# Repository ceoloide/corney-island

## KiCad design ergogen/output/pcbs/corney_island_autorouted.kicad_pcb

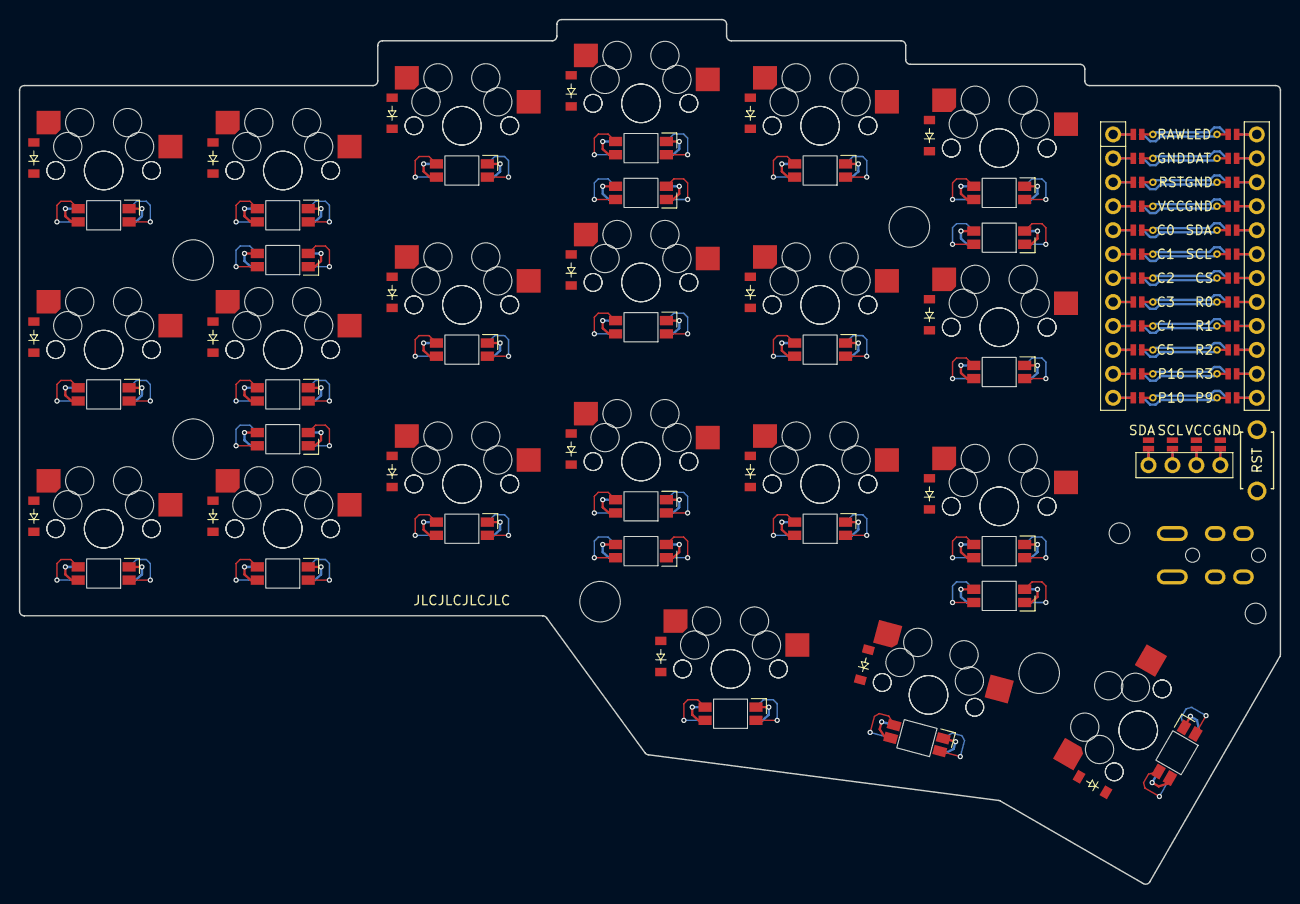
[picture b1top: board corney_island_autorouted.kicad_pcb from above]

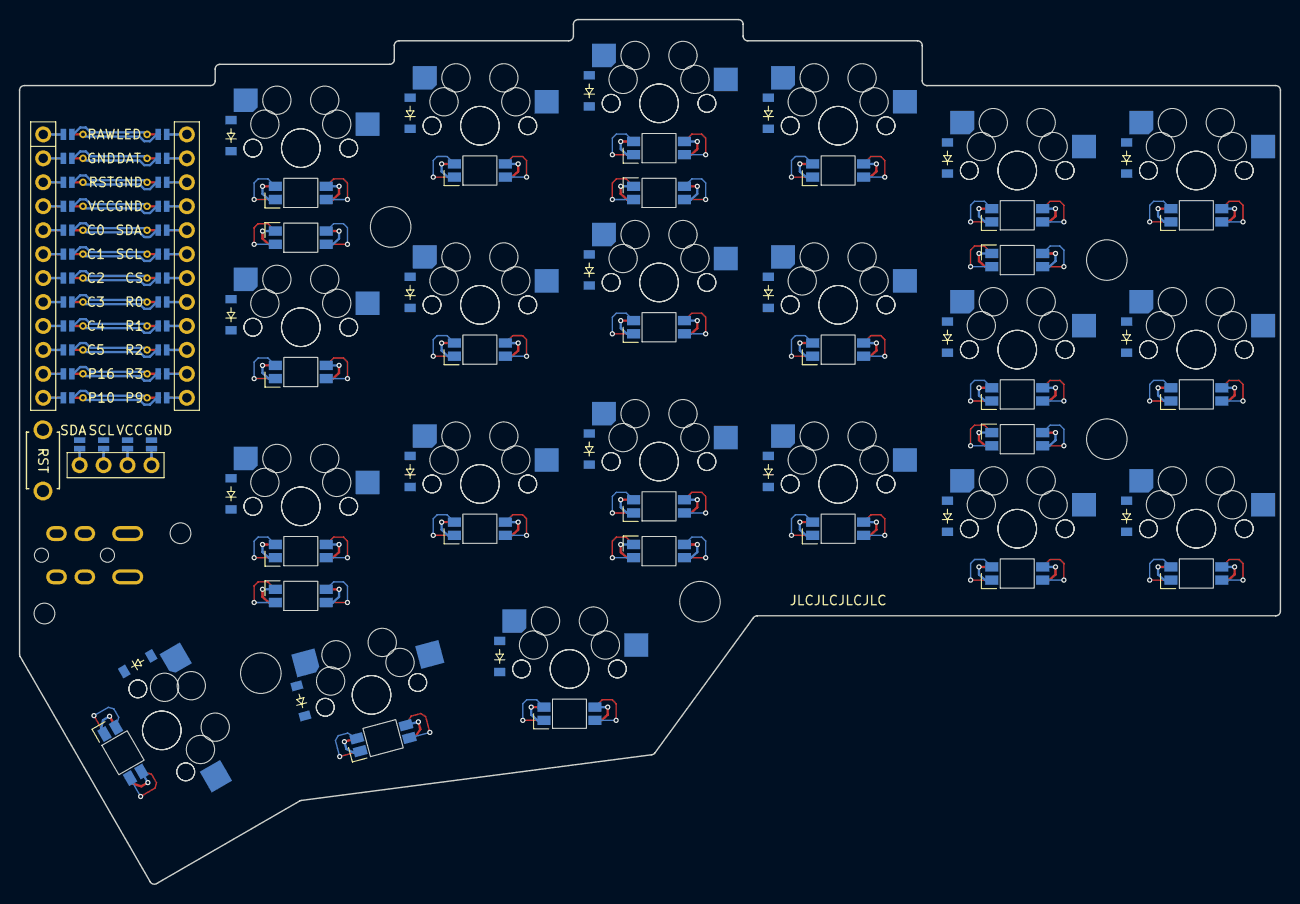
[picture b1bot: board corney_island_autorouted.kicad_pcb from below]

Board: 2 copper layers, 133.8 x 91.7 mm, 122 parts (69 on the bottom side), 101 nets.

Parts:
D1, D2, D3, D4, D5, D6, D7, D8, D9, D10, D11, D12, D13, D14, D15, D16, D17, D18, D19, D20, D21, D22, D23, D24, D25, D26, D27, D28, D29, D30, D31, D32, D33, D34, D35, D36, D37, D38, D39, D40, D41, D42: diode_tht_sod123
DISP1: display_ssd1306
LED1, LED2, LED3, LED4, LED5, LED6, LED7, LED8, LED9, LED10, LED11, LED12, LED13, LED14, LED15, LED16, LED17, LED18, LED19, LED20, LED21: led_SK6812mini-e (per-key, reversible)
LED22, LED23, LED24, LED25, LED26, LED27: led_SK6812mini-e (underglow, reversible)
MCU1: mcu_nice_nano
MH1, MH2, MH3, MH4, MH5, MH6, MH7: mounting_hole_npth
RST1: reset_switch_tht_top
S1, S2, S3, S4, S5, S6, S7, S8, S9, S10, S11, S12, S13, S14, S15, S16, S17, S18, S19, S20, S21, S22, S23, S24, S25, S26, S27, S28, S29, S30, S31, S32, S33, S34, S35, S36, S37, S38, S39, S40, S41, S42: switch_mx
TRRS1: trrs_pj320a (reversible, symmetric)

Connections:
C0: MCU1.120, S1.1, S2.1, S3.1, S22.1, S23.1, S24.1
C1: MCU1.119, S4.1, S5.1, S6.1, S25.1, S26.1, S27.1
C2: MCU1.118, S7.1, S8.1, S9.1, S28.1, S29.1, S30.1
C3: MCU1.117, S10.1, S11.1, S12.1, S19.1, S31.1, S32.1, S33.1, S40.1
C4: MCU1.116, S13.1, S14.1, S15.1, S20.1, S34.1, S35.1, S36.1, S41.1
C5: MCU1.115, S16.1, S17.1, S18.1, S21.1, S37.1, S38.1, S39.1, S42.1
DAT: MCU1.102, TRRS1.3
DISP1_1: DISP1.1, DISP1.10, DISP1.23
DISP1_2: DISP1.2, DISP1.11, DISP1.22
DISP1_3: DISP1.3, DISP1.12, DISP1.21
DISP1_4: DISP1.4, DISP1.13, DISP1.20
GND: DISP1.14, DISP1.24, LED1.3, LED2.3, LED3.3, LED4.3, LED5.3, LED6.3, LED7.3, LED8.3, LED9.3, LED10.3, LED11.3, LED12.3, LED13.3, LED14.3, LED15.3, LED16.3, LED17.3, LED18.3, LED19.3, LED20.3, LED21.3, LED22.3, LED23.3, LED24.3, LED25.3, LED26.3, LED27.3, MCU1.103, MCU1.104, MCU1.123, RST1.2, TRRS1.2
LED: LED22.4, MCU1.101
LED_1: LED16.4, LED21.2
LED_2: LED16.2, LED17.4
LED_3: LED17.2, LED18.4
LED_4: LED15.4, LED18.2
LED_5: LED14.4, LED15.2
LED_6: LED13.4, LED14.2
LED_7: LED13.2, LED20.4
LED_8: LED19.4, LED20.2
LED_9: LED10.4, LED19.2
LED_10: LED10.2, LED11.4
LED_11: LED11.2, LED12.4
LED_12: LED9.4, LED12.2
LED_13: LED8.4, LED9.2
LED_14: LED7.4, LED8.2
LED_15: LED4.4, LED7.2
LED_16: LED4.2, LED5.4
LED_17: LED5.2, LED6.4
LED_18: LED3.4, LED6.2
LED_19: LED2.4, LED3.2
LED_20: LED1.4, LED2.2
MCU1_1: MCU1.1, MCU1.24
MCU1_2: MCU1.2, MCU1.23
MCU1_3: MCU1.3, MCU1.22
MCU1_4: MCU1.4, MCU1.21
MCU1_5: MCU1.5, MCU1.20
MCU1_6: MCU1.6, MCU1.19
MCU1_7: MCU1.7, MCU1.18
MCU1_8: MCU1.8, MCU1.17
MCU1_9: MCU1.9, MCU1.16
MCU1_10: MCU1.10, MCU1.15
MCU1_11: MCU1.11, MCU1.14
MCU1_12: MCU1.12, MCU1.13
R0: D3.1, D6.1, D9.1, D12.1, D15.1, D18.1, D24.1, D27.1, D30.1, D33.1, D36.1, D39.1, MCU1.108
R1: D2.1, D5.1, D8.1, D11.1, D14.1, D17.1, D23.1, D26.1, D29.1, D32.1, D35.1, D38.1, MCU1.109
R2: D1.1, D4.1, D7.1, D10.1, D13.1, D16.1, D22.1, D25.1, D28.1, D31.1, D34.1, D37.1, MCU1.110
R3: D19.1, D20.1, D21.1, D40.1, D41.1, D42.1, MCU1.111
RST: MCU1.122, RST1.1
SCL: DISP1.16, DISP1.26, MCU1.106
SDA: DISP1.17, DISP1.27, MCU1.105
ULED_1: LED22.2, LED23.4
ULED_2: LED23.2, LED24.4
ULED_3: LED24.2, LED25.4
ULED_4: LED25.2, LED26.4
ULED_5: LED26.2, LED27.4
ULED_6: LED21.4, LED27.2
VCC: DISP1.15, DISP1.25, LED1.1, LED2.1, LED3.1, LED4.1, LED5.1, LED6.1, LED7.1, LED8.1, LED9.1, LED10.1, LED11.1, LED12.1, LED13.1, LED14.1, LED15.1, LED16.1, LED17.1, LED18.1, LED19.1, LED20.1, LED21.1, LED22.1, LED23.1, LED24.1, LED25.1, LED26.1, LED27.1, MCU1.121, TRRS1.4
far_home_B: D21.2, S21.2
far_home_F: D42.2, S42.2
index_bottom_B: D13.2, S13.2
index_bottom_F: D34.2, S34.2
index_home_B: D14.2, S14.2
index_home_F: D35.2, S35.2
index_top_B: D15.2, S15.2
index_top_F: D36.2, S36.2
inner_bottom_B: D16.2, S16.2
inner_bottom_F: D37.2, S37.2
inner_home_B: D17.2, S17.2
inner_home_F: D38.2, S38.2
inner_top_B: D18.2, S18.2
inner_top_F: D39.2, S39.2
mid_home_B: D20.2, S20.2
mid_home_F: D41.2, S41.2
middle_bottom_B: D10.2, S10.2
middle_bottom_F: D31.2, S31.2
middle_home_B: D11.2, S11.2
middle_home_F: D32.2, S32.2
middle_top_B: D12.2, S12.2
middle_top_F: D33.2, S33.2
near_home_B: D19.2, S19.2
near_home_F: D40.2, S40.2
outer_bottom_B: D1.2, S1.2
outer_bottom_F: D22.2, S22.2
outer_home_B: D2.2, S2.2
outer_home_F: D23.2, S23.2
outer_top_B: D3.2, S3.2
outer_top_F: D24.2, S24.2
pinky_bottom_B: D4.2, S4.2
pinky_bottom_F: D25.2, S25.2
pinky_home_B: D5.2, S5.2
pinky_home_F: D26.2, S26.2
pinky_top_B: D6.2, S6.2
pinky_top_F: D27.2, S27.2
ring_bottom_B: D7.2, S7.2
ring_bottom_F: D28.2, S28.2
ring_home_B: D8.2, S8.2
ring_home_F: D29.2, S29.2
ring_top_B: D9.2, S9.2
ring_top_F: D30.2, S30.2

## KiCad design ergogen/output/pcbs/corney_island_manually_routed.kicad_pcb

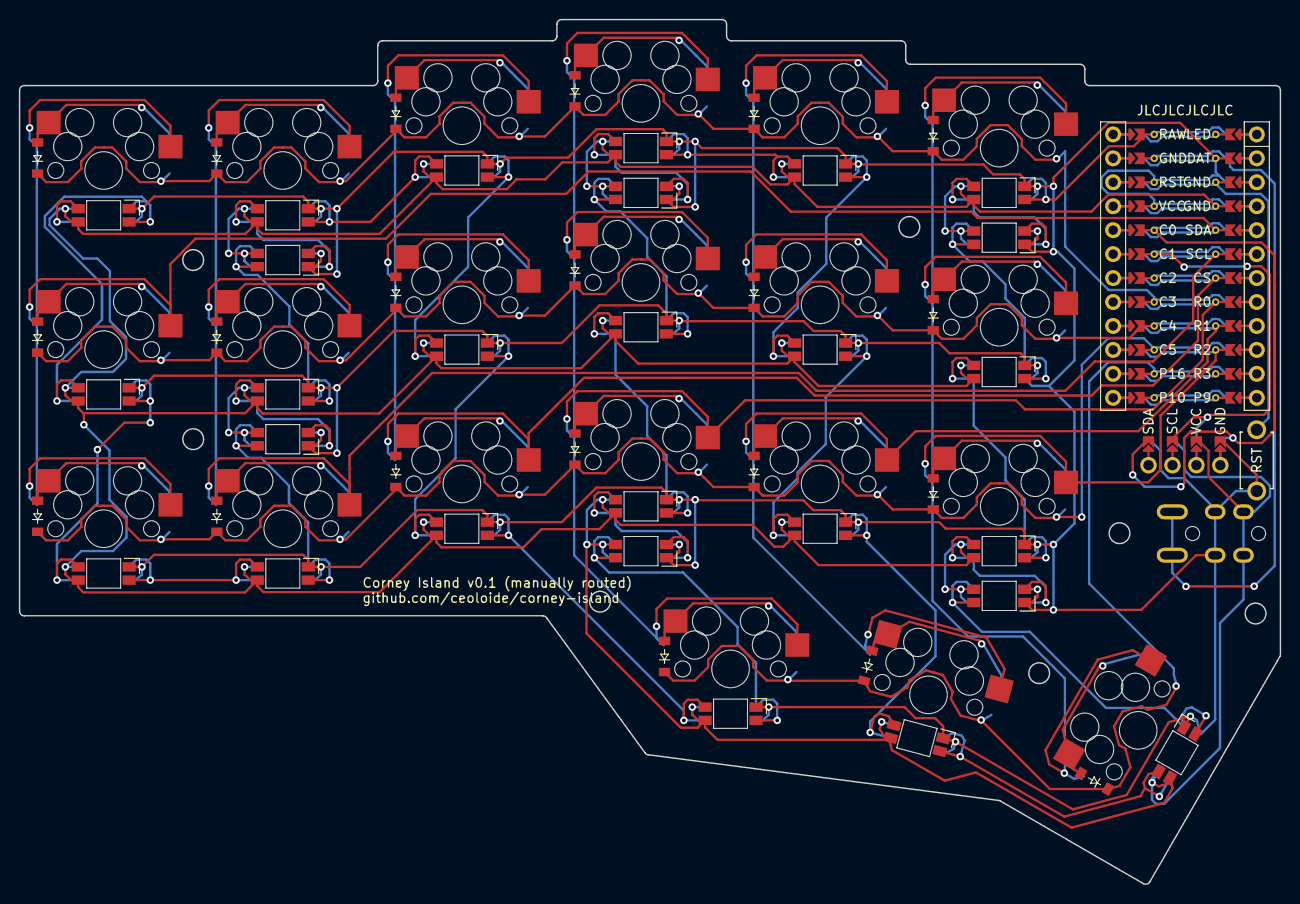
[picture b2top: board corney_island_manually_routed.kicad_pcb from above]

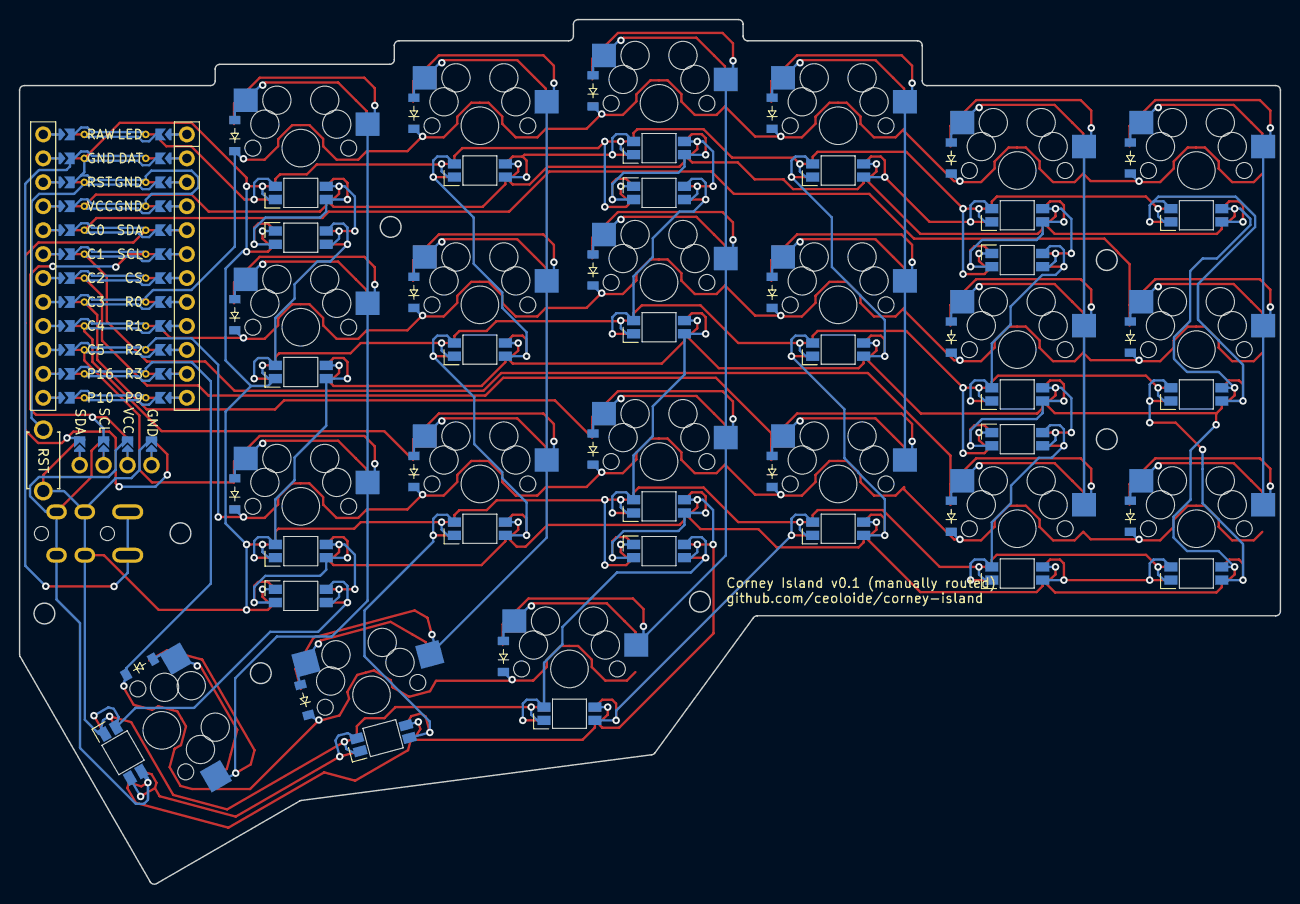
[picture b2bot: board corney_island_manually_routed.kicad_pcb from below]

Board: 2 copper layers, 133.8 x 91.7 mm, 94 parts (48 on the bottom side), 64 nets.

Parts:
B1: Reset (PTS636 SP43 LFS); top-actuated-reset-switch
D1, D2, D3, D4, D5, D6, D7, D8, D9, D10, D11, D12, D13, D14, D15, D16, D17, D18, D19, D20, D21, D22, D23, D24, D25, D26, D27, D28, D29, D30, D31, D32, D33, D34, D35, D36, D37, D38, D39, D40, D41, D42: ComboDiode
LED1, LED2, LED3, LED4, LED5, LED6, LED7, LED8, LED9, LED10, LED11, LED12, LED13, LED14, LED15, LED16, LED17, LED18, LED19, LED20, LED21: YS-SK6812MINI-E (per-key)
LED22, LED23, LED24, LED25, LED26, LED27: YS-SK6812MINI-E (underglow)
LED28: combo_display
MCU1: nice_nano
S1, S2, S3, S4, S5, S6, S7, S8, S9, S10, S11, S12, S13, S14, S15, S16, S17, S18, S19, S20, S21: MX
TRRS1: TRRS-PJ-320A-dual

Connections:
C0: MCU1.5, S1.1, S2.1, S3.1
C1: MCU1.6, S4.1, S5.1, S6.1
C2: MCU1.7, S7.1, S8.1, S9.1
C3: MCU1.8, S10.1, S11.1, S12.1, S19.1
C4: MCU1.9, S13.1, S14.1, S15.1, S20.1
C5: MCU1.10, S16.1, S17.1, S18.1, S21.1
GND: B1.2, LED1.3, LED2.3, LED3.3, LED4.3, LED5.3, LED6.3, LED7.3, LED8.3, LED9.3, LED10.3, LED11.3, LED12.3, LED13.3, LED14.3, LED15.3, LED16.3, LED17.3, LED18.3, LED19.3, LED20.3, LED21.3, LED22.3, LED23.3, LED24.3, LED25.3, LED26.3, LED27.3, LED28.31, LED28.41, MCU1.2, MCU1.121, MCU1.122, TRRS1.3
LED: LED18.4, MCU1.124
LED_1: LED18.2, LED27.4
LED_2: LED16.4, LED17.2
LED_3: LED21.4, LED26.2
LED_4: LED20.4, LED21.2
LED_5: LED13.4, LED20.2
LED_6: LED13.2, LED14.4
LED_7: LED14.2, LED15.4
LED_8: LED12.4, LED15.2
LED_9: LED11.4, LED25.2
LED_10: LED10.4, LED11.2
LED_11: LED19.4, LED24.2
LED_12: LED7.4, LED19.2
LED_13: LED7.2, LED8.4
LED_14: LED8.2, LED9.4
LED_15: LED6.4, LED9.2
LED_16: LED5.4, LED23.2
LED_17: LED4.4, LED22.2
LED_18: LED1.4, LED4.2
LED_19: LED1.2, LED2.4
LED_20: LED2.2, LED3.4
P2: LED28.34, LED28.44, MCU1.120
P3: LED28.33, LED28.43, MCU1.119
R0: D3.1, D6.1, D9.1, D12.1, D15.1, D18.1, D24.1, D27.1, D30.1, D33.1, D36.1, D39.1, MCU1.117
R1: D2.1, D5.1, D8.1, D11.1, D14.1, D17.1, D23.1, D26.1, D29.1, D32.1, D35.1, D38.1, MCU1.116
R2: D1.1, D4.1, D7.1, D10.1, D13.1, D16.1, D22.1, D25.1, D28.1, D31.1, D34.1, D37.1, MCU1.115
R3: D19.1, D20.1, D21.1, D40.1, D41.1, D42.1, MCU1.114
RST: B1.1, MCU1.3
ULED_1: LED17.4, LED27.2
ULED_2: LED16.2, LED26.4
ULED_3: LED12.2, LED25.4
ULED_4: LED10.2, LED24.4
ULED_5: LED6.2, LED23.4
ULED_6: LED5.2, LED22.4
VCC: LED1.1, LED2.1, LED3.1, LED4.1, LED5.1, LED6.1, LED7.1, LED8.1, LED9.1, LED10.1, LED11.1, LED12.1, LED13.1, LED14.1, LED15.1, LED16.1, LED17.1, LED18.1, LED19.1, LED20.1, LED21.1, LED22.1, LED23.1, LED24.1, LED25.1, LED26.1, LED27.1, LED28.32, LED28.42, MCU1.4, TRRS1.4
data: MCU1.123, TRRS1.1
far_home: D21.2, D42.2, S21.2
index_bottom: D13.2, D34.2, S13.2
index_home: D14.2, D35.2, S14.2
index_top: D15.2, D36.2, S15.2
inner_bottom: D16.2, D37.2, S16.2
inner_home: D17.2, D38.2, S17.2
inner_top: D18.2, D39.2, S18.2
mid_home: D20.2, D41.2, S20.2
middle_bottom: D10.2, D31.2, S10.2
middle_home: D11.2, D32.2, S11.2
middle_top: D12.2, D33.2, S12.2
near_home: D19.2, D40.2, S19.2
outer_bottom: D1.2, D22.2, S1.2
outer_home: D2.2, D23.2, S2.2
outer_top: D3.2, D24.2, S3.2
pinky_bottom: D4.2, D25.2, S4.2
pinky_home: D5.2, D26.2, S5.2
pinky_top: D6.2, D27.2, S6.2
ring_bottom: D7.2, D28.2, S7.2
ring_home: D8.2, D29.2, S8.2
ring_top: D9.2, D30.2, S9.2

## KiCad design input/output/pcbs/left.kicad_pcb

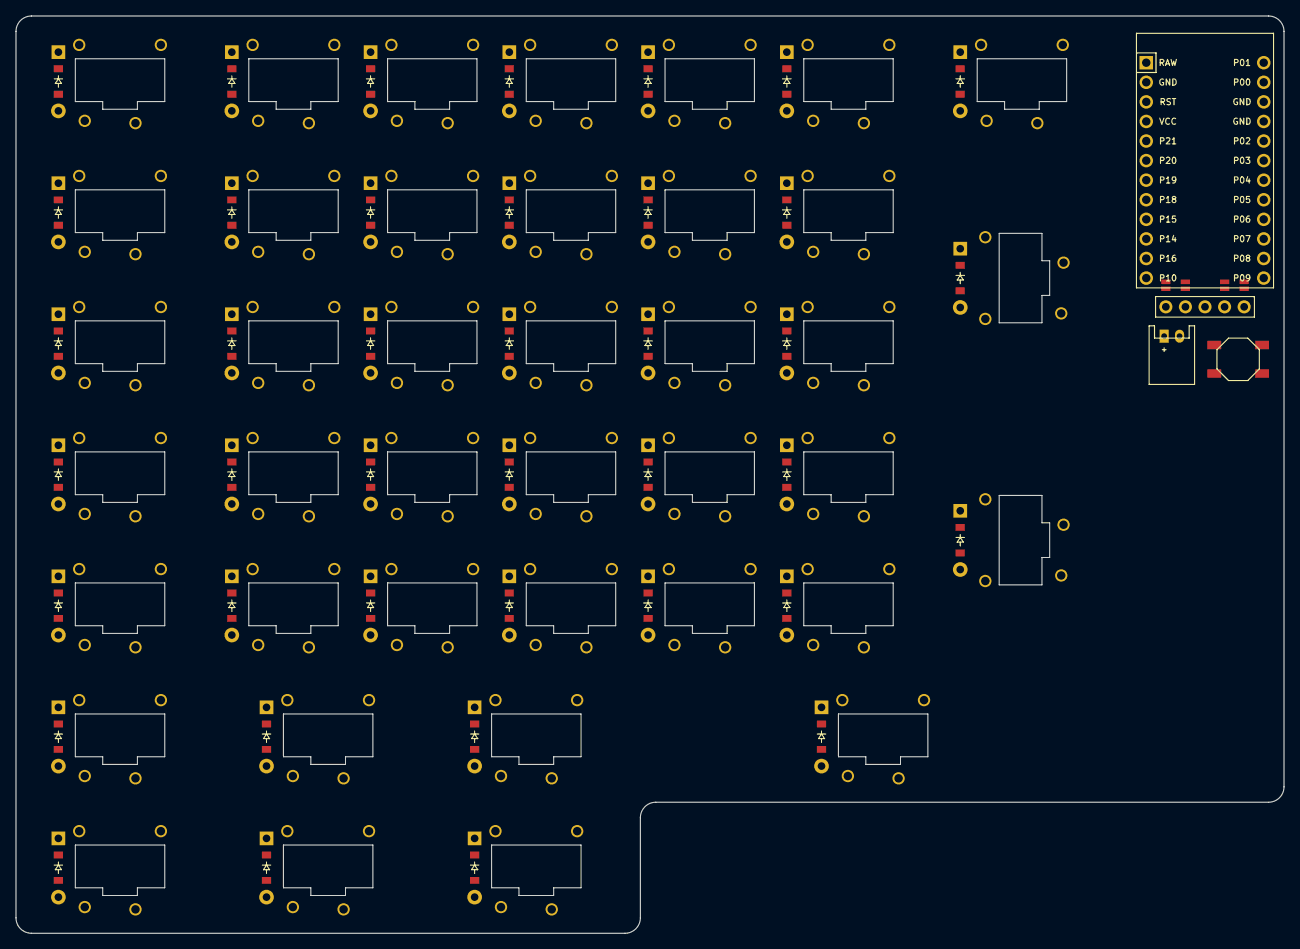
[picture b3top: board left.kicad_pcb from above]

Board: 2 copper layers, 164.5 x 119.0 mm, 84 parts (0 on the bottom side), 65 nets, no tracks yet.

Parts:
B1: SW_TACT_ALPS_SKQGABE010
D1, D2, D3, D4, D5, D6, D7, D8, D9, D10, D11, D12, D13, D14, D15, D16, D17, D18, D19, D20, D21, D22, D23, D24, D25, D26, D27, D28, D29, D30, D31, D32, D33, D34, D35, D36, D37, D38, D39, D40: ComboDiode
DISP1: nice!view
JST1: JST_PH_S2B-PH-K_02x2.00mm_Angled
MCU1: ProMicro
S1, S2, S3, S4, S5, S6, S7, S8, S9, S10, S11, S12, S13, S14, S15, S16, S17, S18, S19, S20, S21, S22, S23, S24, S25, S26, S27, S28, S29, S30, S31, S32, S33, S34, S35, S36, S37, S38, S39, S40: Kailh_PG1232

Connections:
BAT_P: JST1.1, MCU1.1
C0: MCU1.5, S1.2, S2.2, S3.2, S4.2, S5.2, S31.2, S32.2
C1: MCU1.6, S6.2, S7.2, S8.2, S9.2, S10.2, S33.2, S34.2
C2: MCU1.7, S11.2, S12.2, S13.2, S14.2, S15.2, S35.2, S36.2
C3: MCU1.8, S16.2, S17.2, S18.2, S19.2, S20.2
C4: MCU1.9, S21.2, S22.2, S23.2, S24.2, S25.2, S38.2
C5: MCU1.10, S26.2, S27.2, S28.2, S29.2, S30.2
C6: MCU1.11, S37.2, S39.2, S40.2
DISP1_1: DISP1.1, DISP1.10, DISP1.23
DISP1_2: DISP1.2, DISP1.11, DISP1.22
DISP1_4: DISP1.4, DISP1.12, DISP1.21
DISP1_5: DISP1.5, DISP1.13, DISP1.20
DPC: DISP1.15, DISP1.25, MCU1.13
DPD: DISP1.14, DISP1.24, MCU1.14
DPE: DISP1.17, DISP1.27, MCU1.17
GND: B1.1, DISP1.16, DISP1.26, JST1.2, MCU1.2, MCU1.15, MCU1.16
R0: D5.1, D10.1, D15.1, D20.1, D25.1, D30.1, D39.1
R1: D4.1, D9.1, D14.1, D19.1, D24.1, D29.1, D38.1, MCU1.18
R2: D3.1, D8.1, D13.1, D18.1, D23.1, D28.1, D37.1, MCU1.19
R3: D2.1, D7.1, D12.1, D17.1, D22.1, D27.1, MCU1.20
R4: D1.1, D6.1, D11.1, D16.1, D21.1, D26.1, MCU1.21
R6: D32.1, D34.1, D36.1, D40.1, MCU1.23
R7: D31.1, D33.1, D35.1, MCU1.24
RST: B1.2, MCU1.3
VCC: DISP1.3, MCU1.4
e_bottom: D16.2, S16.1
e_f: D20.2, S20.1
e_home: D17.2, S17.1
e_num: D19.2, S19.1
e_top: D18.2, S18.1
left_bottom: D1.2, S1.1
left_f: D5.2, S5.1
left_home: D2.2, S2.1
left_num: D4.2, S4.1
left_top: D3.2, S3.1
one_back: D38.2, S40.1
one_down: D31.2, S31.1
one_enter: D37.2, S39.1
one_f: D39.2, S37.1
one_up: D32.2, S32.1
q_bottom: D6.2, S6.1
q_f: D10.2, S10.1
q_home: D7.2, S7.1
q_num: D9.2, S9.1
q_top: D8.2, S8.1
r_bottom: D21.2, S21.1
r_f: D25.2, S25.1
r_home: D22.2, S22.1
r_num: D24.2, S24.1
r_top: D23.2, S23.1
space_space: D40.2, S38.1
t_bottom: D26.2, S26.1
t_f: D30.2, S30.1
t_home: D27.2, S27.1
t_num: D29.2, S29.1
t_top: D28.2, S28.1
three_down: D35.2, S35.1
three_up: D36.2, S36.1
two_down: D33.2, S33.1
two_up: D34.2, S34.1
w_bottom: D11.2, S11.1
w_f: D15.2, S15.1
w_home: D12.2, S12.1
w_num: D14.2, S14.1
w_top: D13.2, S13.1
